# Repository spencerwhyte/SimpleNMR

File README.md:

Simple NMR
==============
This is my first adventure into NMR and I want to keep everything as simple as possible for the first design. 

The process goes a little something like this.

1. Apply a pre-polarizing pulse to the sample.
2. Transmit 90 degree pulse
3. Listen to the FID

Transmit/Receive Board
----------

There is a board which controls the polarization, transmission amplification, and receiver amplification. kicad designs for this board can be found in the RelayBoard folder.

To elaborate on the simple process described above, here is what actually happens.

1. Apply a pre-polarizing pulse to the sample
	- Configure the relays to disable transmit and receive functionality (To protect the electronics)
	- Turn on the polarization coil
	- Wait some fixed period of time
	- Turn off the polarization coil 

2. Transmit 90 degree pulse
	- Configure the relays to allow transmission
	- Tell GNURadio to output a sine wave at the larmour frequency to the sound card/audio interface
	- Wait 90 degrees worth of time
	- Tell GNURadio to stop the output
	- Configure the relays to disable transmission

3. Listen to the FID
	- Configure the relays to enable receiving
	- Tell GNURadio to record from line-in 
	- Apply a Peak hold FFT to the input signal to see what we received

Amplification Board
------------

There is another board which amplifies the transmitted and received signals. kicad designs for the amplifier board can be found in the AmplifierBoard folder.

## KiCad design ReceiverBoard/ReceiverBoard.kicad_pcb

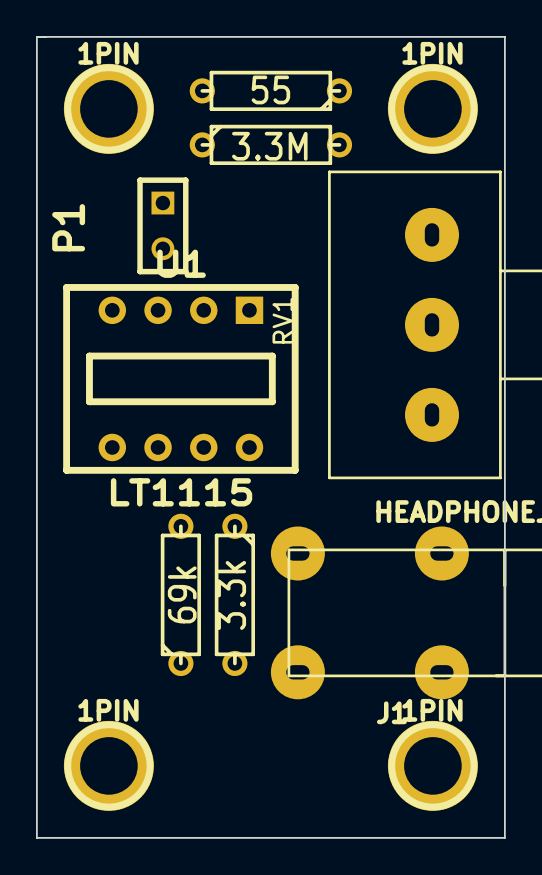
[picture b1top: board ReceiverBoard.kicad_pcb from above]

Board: 2 copper layers, 26.0 x 44.5 mm, 12 parts (0 on the bottom side), 6 nets, no tracks yet.

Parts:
1PIN, 1PIN#2, 1PIN#3, 1PIN#4: P***; 1pin
J1: HEADPHONEJACK; HeadphoneJack
P1: CONN_2; PinHeader2
R1: 3.3M; R3
R2: 55; R3
R3: 69k; R3
R4: 3.3k; R3
RV1: POT; POT_P160KN
U1: LT1115; SWDIP4

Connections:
GND: J1.1, P1.1, R2.2, R4.1
unnamed: R1.2, R2.1, RV1.1
unnamed: R3.2, RV1.2, U1.6
unnamed: J1.2, R3.1, R4.2
unnamed: R1.1, U1.2
unnamed: P1.2, U1.3

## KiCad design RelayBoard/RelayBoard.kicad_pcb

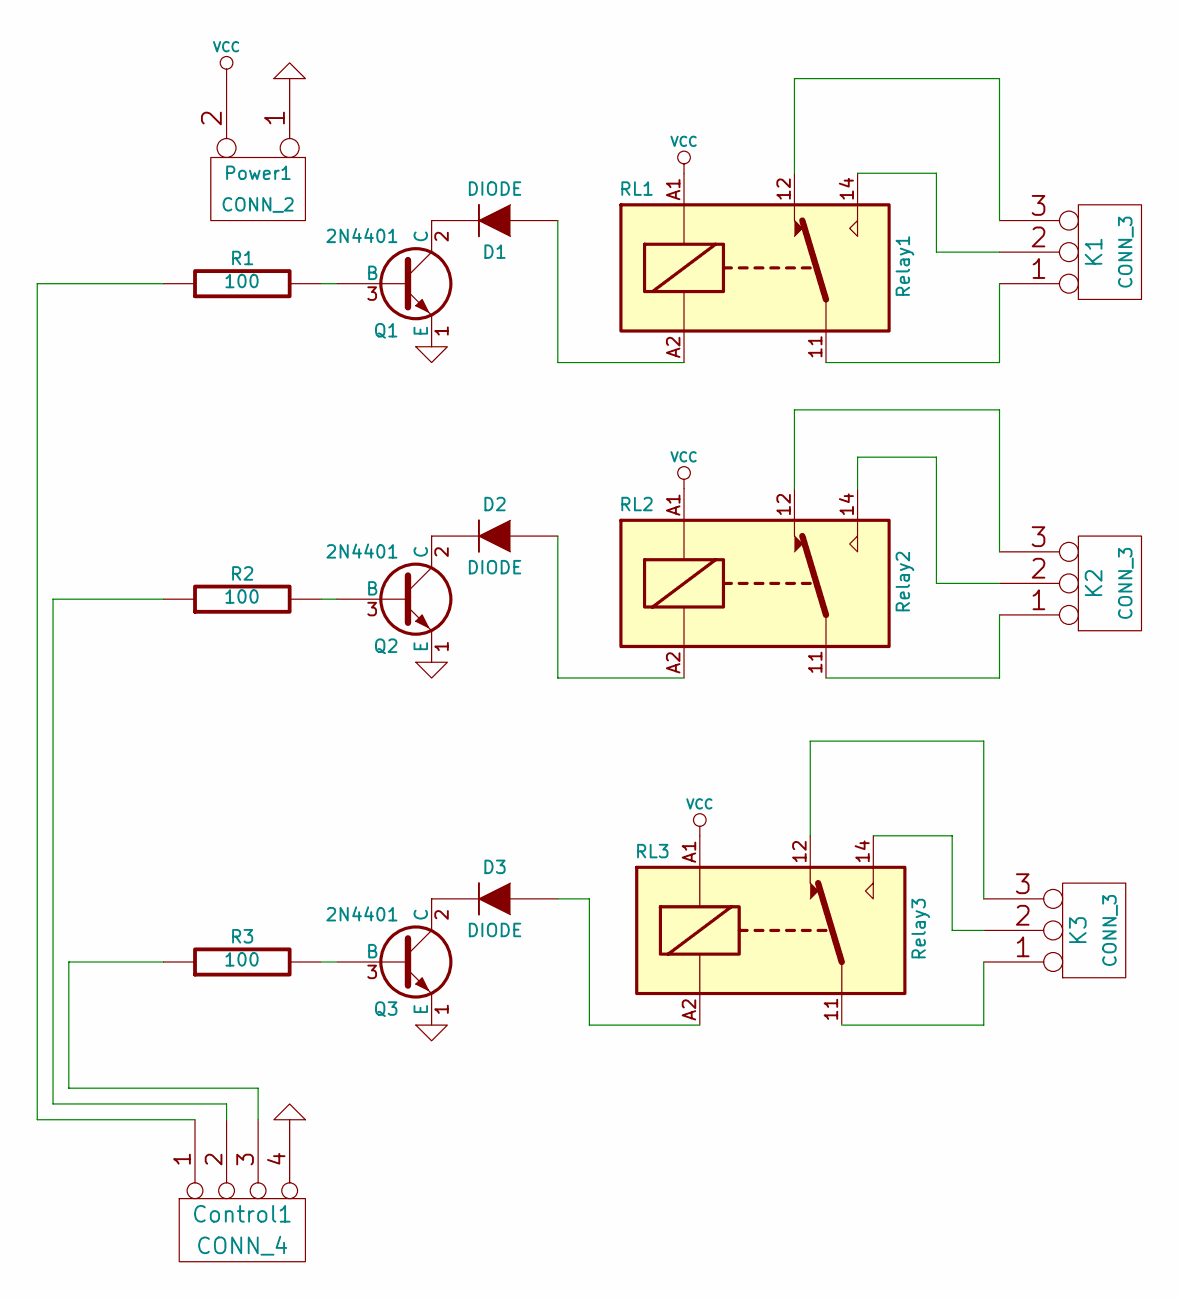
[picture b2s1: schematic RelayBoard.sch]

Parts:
Control1: CONN_4
D1, D2, D3: DIODE
K1, K2, K3: CONN_3
Power1: CONN_2
Q1, Q2, Q3: 2N4401
R1, R2, R3: 100
RL1: Relay1
RL2: Relay2
RL3: Relay3

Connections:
GND: Control1.4, Power1.1, Q1.1 (E), Q2.1 (E), Q3.1 (E)
unnamed: K2.3, RL2.12
unnamed: K2.1, RL2.11
unnamed: K3.3, RL3.12
unnamed: K3.2 (PM), RL3.14
unnamed: K3.1, RL3.11
unnamed: K2.2 (PM), RL2.14
unnamed: K1.2 (PM), RL1.14
unnamed: K1.3, RL1.12
unnamed: K1.1, RL1.11
unnamed: D3.2 (K), Q3.2 (C)
unnamed: D2.2 (K), Q2.2 (C)
unnamed: D1.2 (K), Q1.2 (C)
unnamed: Q3.3 (B), R3.2
unnamed: Control1.3, R3.1
unnamed: Q2.3 (B), R2.2
unnamed: Q1.3 (B), R1.2
unnamed: Control1.1, R1.1
unnamed: D3.1 (A), RL3.A2
unnamed: D2.1 (A), RL2.A2
unnamed: D1.1 (A), RL1.A2
unnamed: Control1.2, R2.1
VCC: Power1.2 (PM), RL1.A1, RL2.A1, RL3.A1

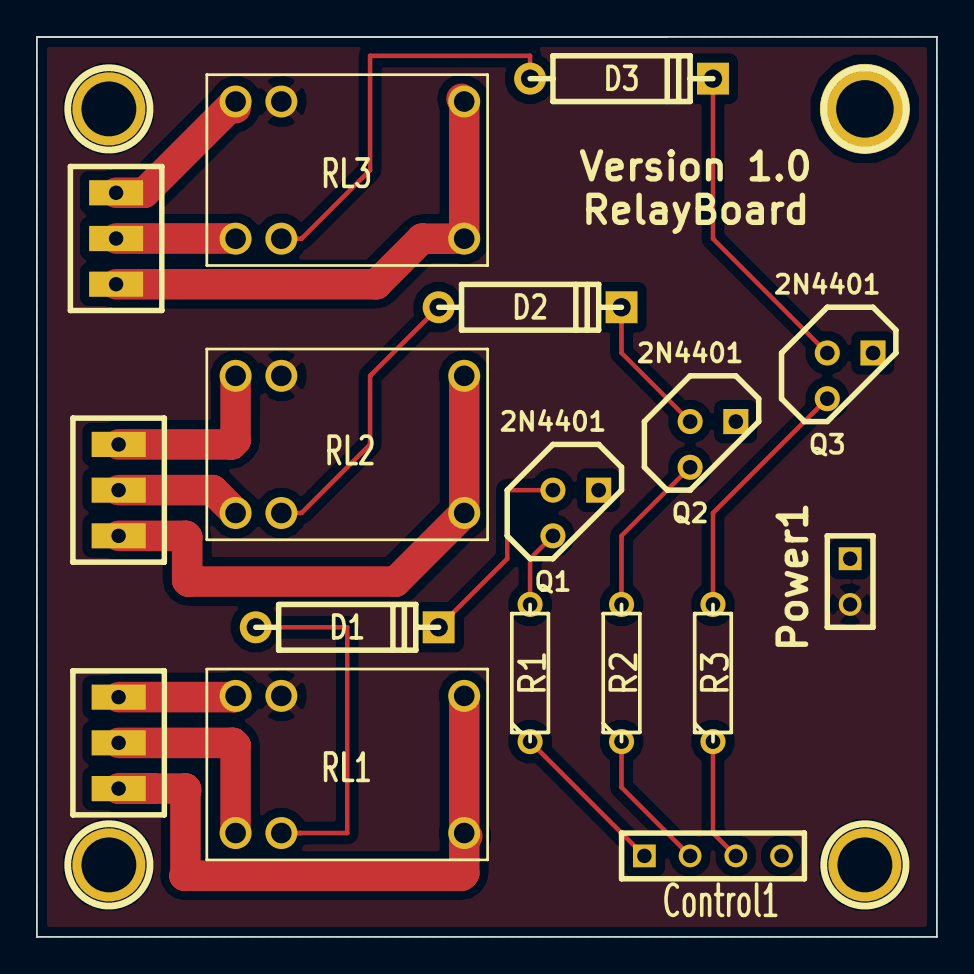
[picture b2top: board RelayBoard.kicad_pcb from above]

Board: 2 copper layers, 50.0 x 50.0 mm, 21 parts (0 on the bottom side), 23 nets.

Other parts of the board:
1PIN, 1PIN#2, 1PIN#3, 1PIN#4: P***; 1pin

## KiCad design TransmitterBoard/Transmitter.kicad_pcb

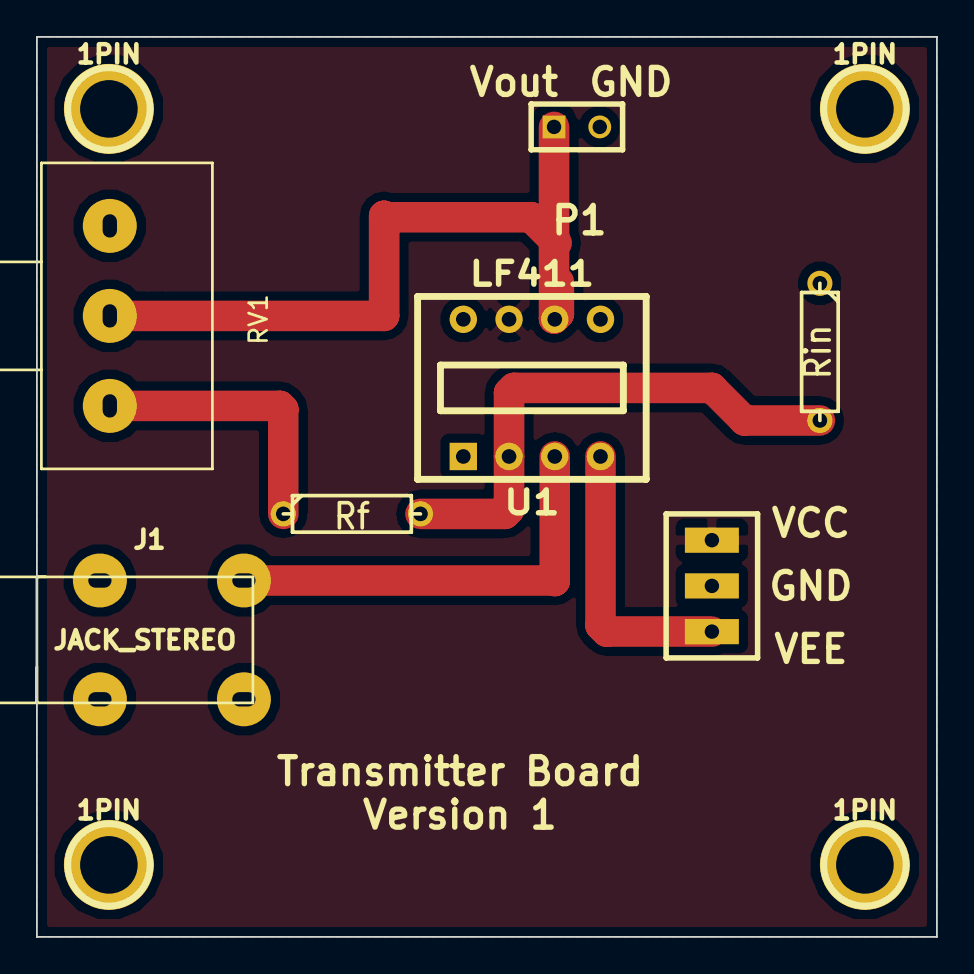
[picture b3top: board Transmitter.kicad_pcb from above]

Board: 2 copper layers, 50.0 x 50.0 mm, 11 parts (0 on the bottom side), 7 nets.

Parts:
1PIN, 1PIN#2, 1PIN#3, 1PIN#4: P***; 1pin
J1: JACK_STEREO; HeadphoneJack
K1: CONN_3; PinHeader3
P1: CONN_2; PinHeader2
R1: Rin; R3
R2: Rf; R3
RV1: 10k; POT_P160KN
U1: LF411; SWDIP4

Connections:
GND: J1.1, K1.2, P1.2, R1.1
unnamed: R1.2, R2.2, U1.2
unnamed: J1.2, U1.3
unnamed: P1.1, RV1.2, U1.6
unnamed: R2.1, RV1.1
VCC: K1.1, U1.7
VEE: K1.3, U1.4

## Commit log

2014-04-16 Initial commit of last weeks work
2014-04-16 Began to define the electronics interface
2014-04-19 Began testing of relay switching speed
2014-04-19 Tested out electronics and audio in a slowed down version of a 90 degree CW experiment
2014-05-05 Added kicad board design
2014-05-05 Added explanation of folders within the project
2014-05-05 Completed RelayBoard PCB Design
2014-05-06 Fixed pin header spacing on all connectors
2014-05-11 Added transmitter amplifier board and the corresponding gerbers
2014-05-11 Completed receiver schematic+footprints+90% of the PCB
2014-05-12 Finished adding record to file for the FID
2014-05-18 Made timing code more accurate
